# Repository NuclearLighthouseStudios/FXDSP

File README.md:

# FXDSP — A WhateverDSP based guitar pedal

FXDSP is an easily programmable DSP platform in a familiar guitar pedal form factor:

It's based around an STM32F405 microcontroller and runs on the [WhateverDSP framework](https://github.com/NuclearLighthouseStudios/WhateverDSP),
offering low latency audio processing and fully class complicant USB audio and MIDI support.

FXDSP has interchangeable user interface PCBs so it can easily be tailored to the needs of each effect produced on the platform.

For more information about WhateverDSP, [please see the WhateverDSP repository](https://github.com/NuclearLighthouseStudios/WhateverDSP).

## Example code

Here is a full example showing a simple volume control that scales the audio level using a potentiometer:

```c
#include <libwdsp.h>

void wdsp_init(void)
{
	io_digital_out(BYPASS_L, true);
	io_digital_out(BYPASS_R, true);
}

void wdsp_process(float *in_buffer[BLOCK_SIZE], float *out_buffer[BLOCK_SIZE])
{
	float volume = io_analog_in(POT_1);

	for (int i = 0; i < BLOCK_SIZE; i++)
	{
		float l_sample = in_buffer[0][i];
		float r_sample = in_buffer[1][i];

		out_buffer[0][i] = l_sample * volume;
		out_buffer[1][i] = r_sample * volume;
	}
}

```

Check out the [examples repository](https://github.com/NuclearLighthouseStudios/WhateverDSP-Examples) for more,
or [come chat with us on Discord](https://github.com/NuclearLighthouseStudios/FXDSP#chat).

## Chat

[You can chat with us on Discord.](https://discord.gg/WDsFnartXb)

## License

FXDSP hardware is licensed under CC-BY-NC-SA.

The WhateverDSP library is licensed under GNU Lesser General Public License.

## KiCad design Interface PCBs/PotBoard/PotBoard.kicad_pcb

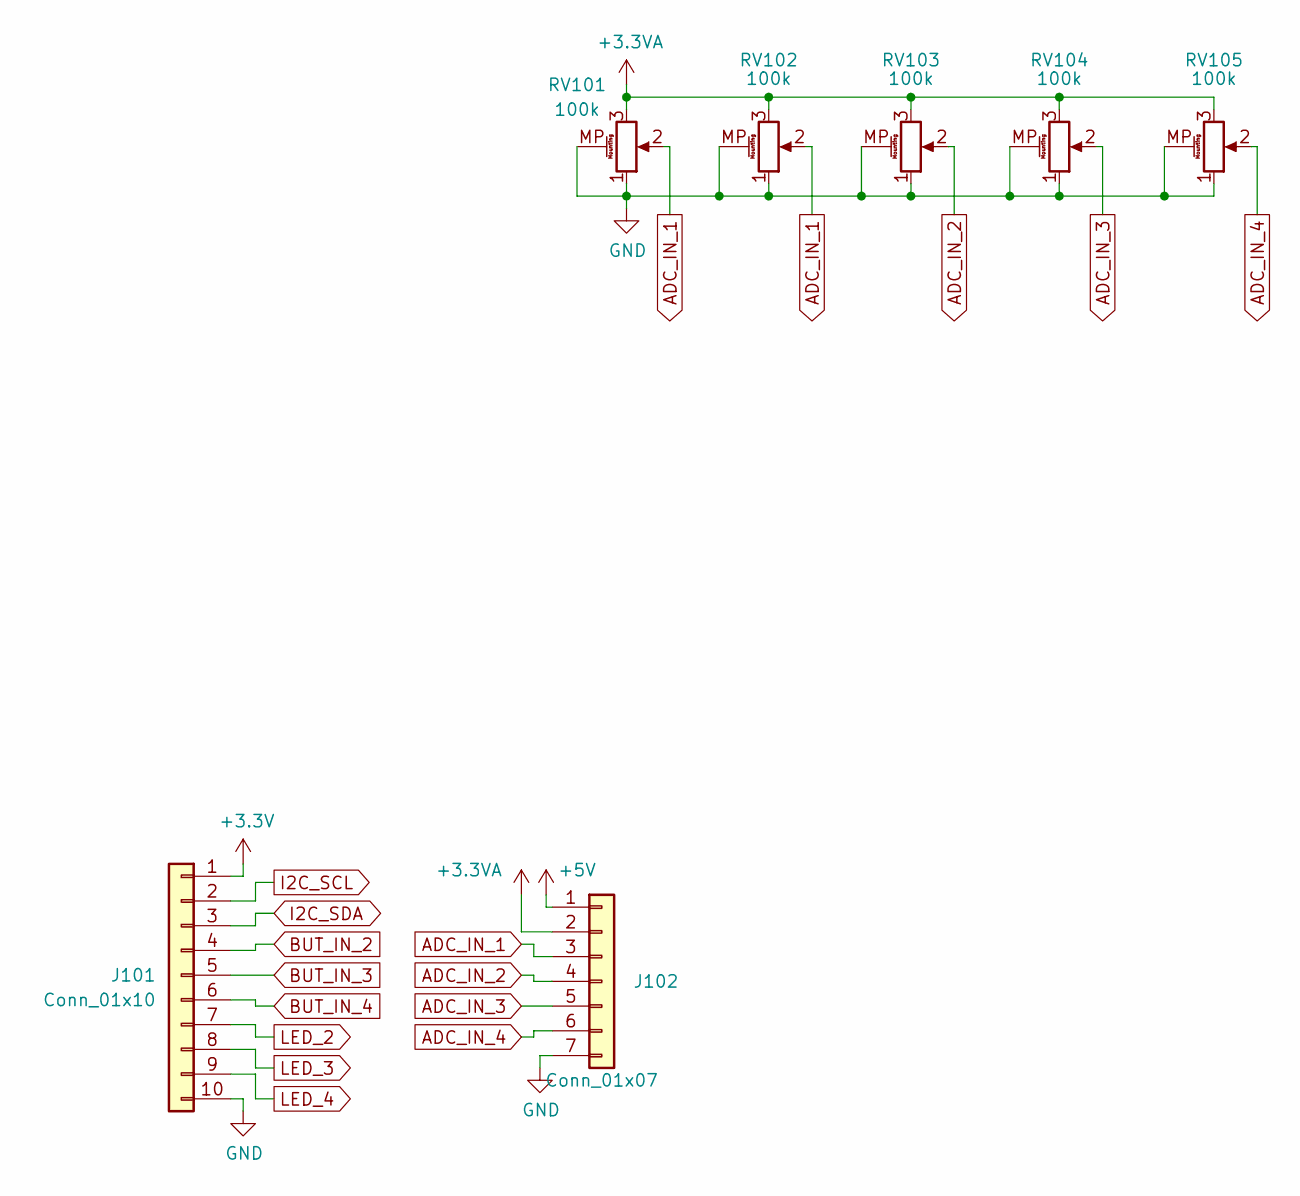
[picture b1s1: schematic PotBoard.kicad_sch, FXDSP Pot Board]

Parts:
J101: Conn_01x10; PinHeader_1x10_P2.54mm_Vertical
J102: Conn_01x07; PinHeader_1x07_P2.54mm_Vertical
RV101, RV102, RV103, RV104, RV105: 100k; Potentiometer_Alps_RK09K_Single_Vertical

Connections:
+3.3V: J101.1
+3.3VA: J102.2, RV101.3, RV102.3, RV103.3, RV104.3, RV105.3
+5V: J102.1
ADC_IN_1: J102.3, RV101.2, RV102.2
ADC_IN_2: J102.4, RV103.2
ADC_IN_3: J102.5, RV104.2
ADC_IN_4: J102.6, RV105.2
BUT_IN_2: J101.4
BUT_IN_3: J101.5
BUT_IN_4: J101.6
GND: J101.10, J102.7, RV101.1, RV101.MP (MountPin), RV102.1, RV102.MP (MountPin), RV103.1, RV103.MP (MountPin), RV104.1, RV104.MP (MountPin), RV105.1, RV105.MP (MountPin)
I2C_SCL: J101.2
I2C_SDA: J101.3
LED_2: J101.7
LED_3: J101.8
LED_4: J101.9

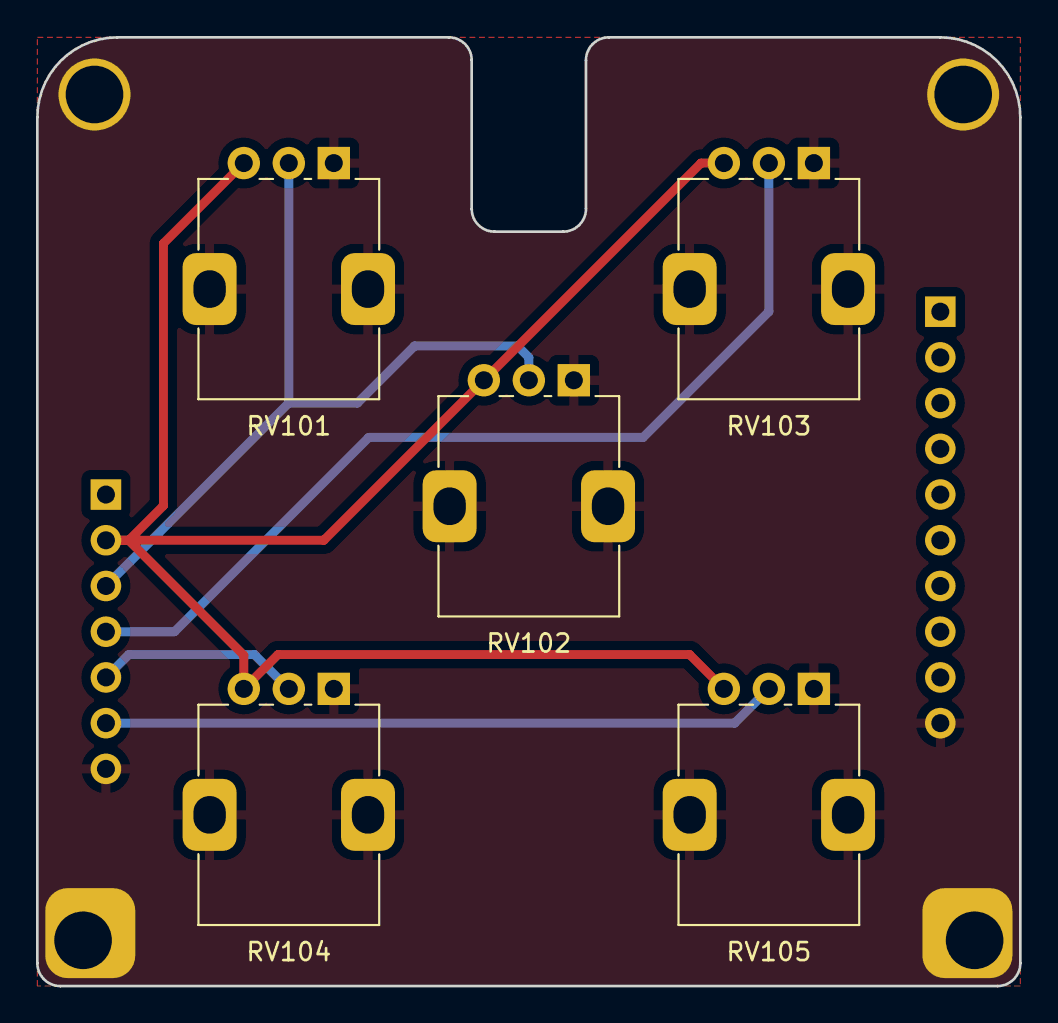
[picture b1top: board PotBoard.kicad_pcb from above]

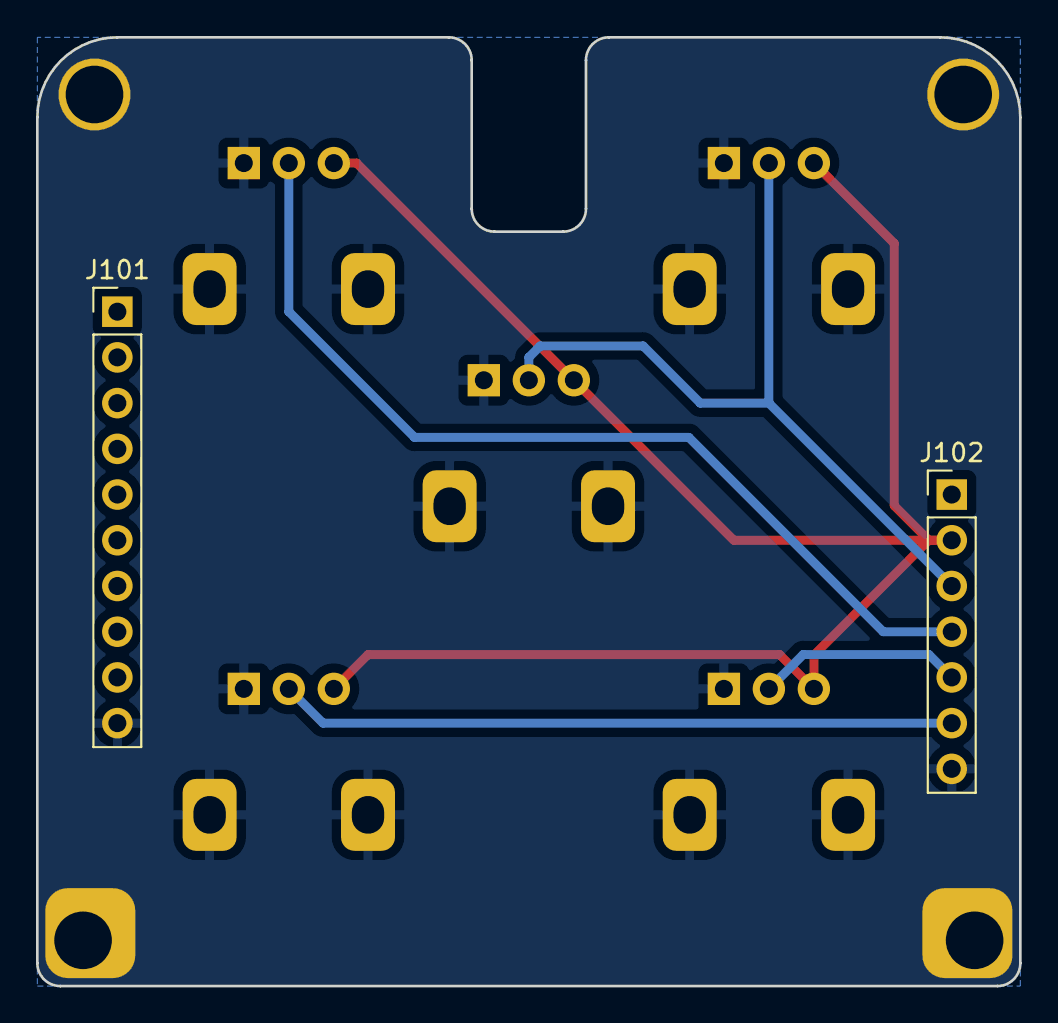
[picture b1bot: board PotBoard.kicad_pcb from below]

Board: 2 copper layers, 54.6 x 52.7 mm, 7 parts (2 on the bottom side), 6 nets.

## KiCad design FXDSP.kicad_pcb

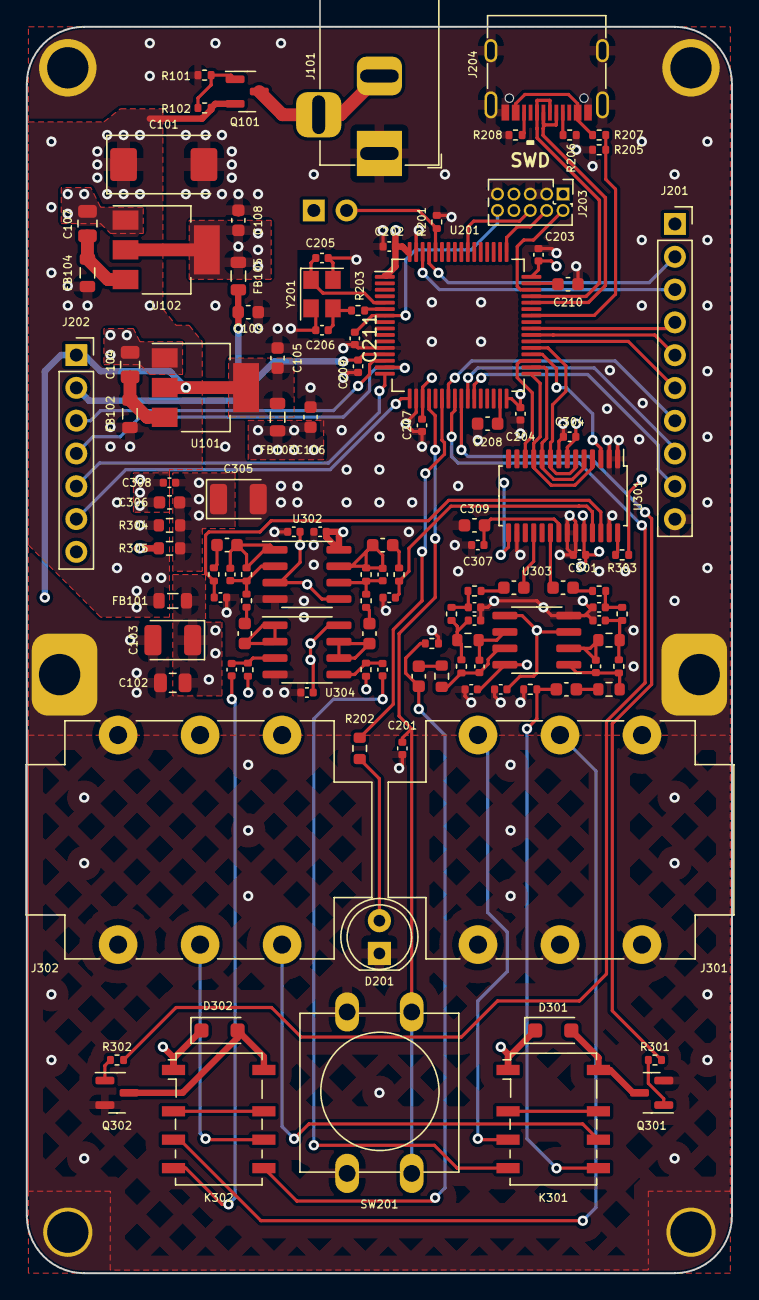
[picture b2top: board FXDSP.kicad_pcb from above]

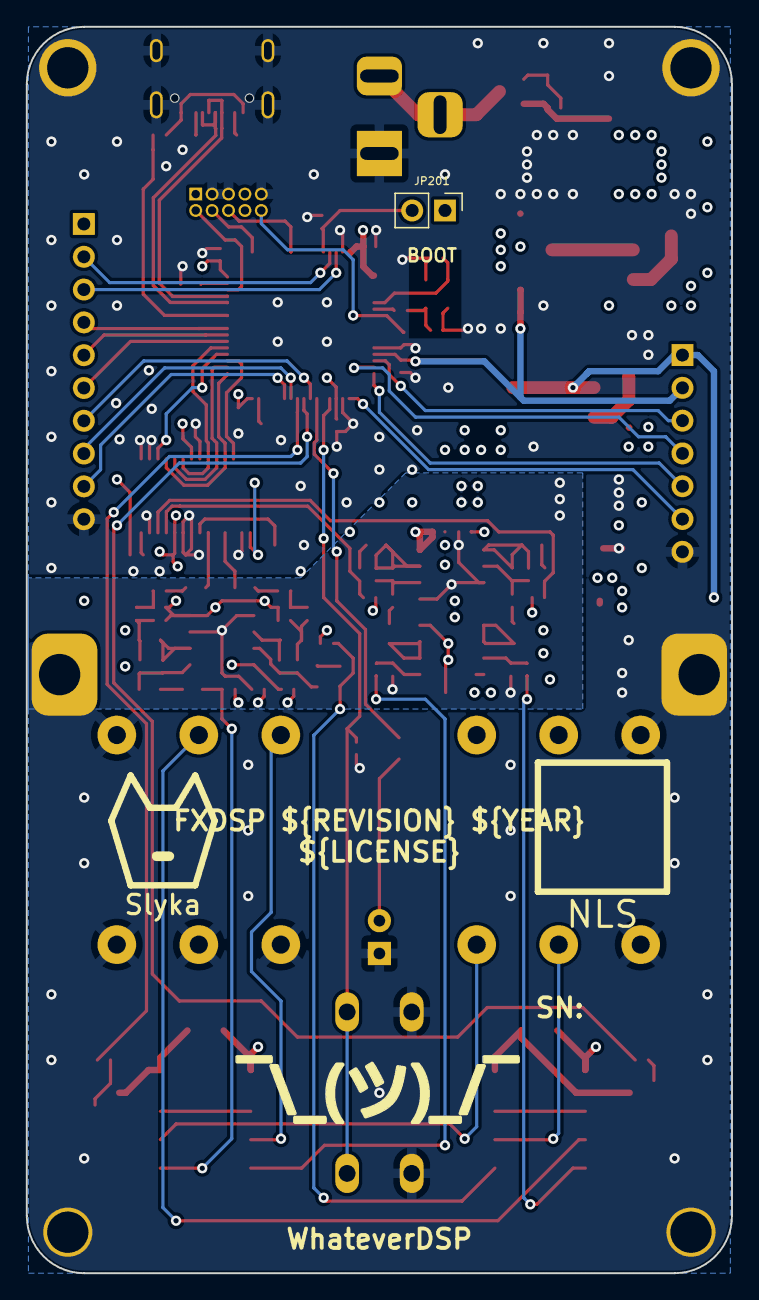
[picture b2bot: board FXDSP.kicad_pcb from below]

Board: 4 copper layers, 54.6 x 96.5 mm, 124 parts (3 on the bottom side), 94 nets.

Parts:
C101: 100µ; CP_EIA-7343-30_AVX-N
C102, C104, C107: 10µ; C_0805_2012Metric
C103: 47µ; CP_EIA-3528-21_Kemet-B
C105, C106, C108, C109, C306, C309, C312, C313, C316, C317, C327, C328, C329, C330: 10µ; C_0603_1608Metric
C201, C202, C203, C204, C207, C209, C211, C301, C302, C303, C304, C307, C308, C322, C325, C326, C331, C332: 100n; C_0402_1005Metric
C205, C206: 12pF; C_0402_1005Metric
C208, C210: 2.2µ; C_0603_1608Metric
C305: 100µ; CP_EIA-3528-21_Kemet-B
C310, C311: 1n; C_0402_1005Metric
C314, C315: 3.3n; C_0402_1005Metric
C318, C319: 150p; C_0402_1005Metric
C320, C321: 330p; C_0402_1005Metric
C323, C324: 10p; C_0402_1005Metric
D201: LED; LED_D5.0mm
D301, D302: SM4007; D_SOD-123F
FB101, FB103, FB105: 600; L_0805_2012Metric
FB102, FB104: 100; L_0805_2012Metric
H101, H102, H103, H104, H105, H106: MountingHole_Pad; MountingHole_3.2mm_M3_Pad
J101: Barrel_Jack_Switch; BarrelJack_Horizontal
J201: Conn_01x10; PinSocket_1x10_P2.54mm_Vertical
J202: Conn_01x07; PinSocket_1x07_P2.54mm_Vertical
J203: Conn_ARM_JTAG_SWD_10; PinHeader_2x05_P1.27mm_Vertical
J204: USB_C_Receptacle_USB2.0; USB_C_Receptacle_G-Switch_GT-USB-7010ASV
J301, J302: AudioJack3_Switch; Jack_6.35mm_Neutrik_NMJ6HCD2_Horizontal
JP201: Boot Jumper; PinHeader_1x02_P2.54mm_Vertical
K301, K302: G6K-2; Relay_DPDT_Omron_G6K-2F-Y
Q101: Si2301CDS; SOT-23
Q301, Q302: MMBT3904; SOT-23
R101: 22k; R_0402_1005Metric
R102, R201, R318, R319: 10k; R_0402_1005Metric
R202: 1k; R_0603_1608Metric
R203: 47; R_0402_1005Metric
R205: 2.2k; R_0402_1005Metric
R206, R208: 5.1k; R_0402_1005Metric
R207, R301, R302, R306, R307: 1k; R_0402_1005Metric
R303: 220k; R_0402_1005Metric
R304, R305: 10k; R_0603_1608Metric
R308, R309: 910; R_0402_1005Metric
R310, R311: 47k; R_0402_1005Metric
R312, R313: 8.6k; R_0402_1005Metric
R314, R316: 43k; R_0402_1005Metric
R315, R317: 130k; R_0603_1608Metric
R320, R321: 100; R_0603_1608Metric
R322, R323, R324, R325: 1M; R_0402_1005Metric
SW201: SW_Push; SW_PUSH-12mm
U101: NCP1117-5.0; SOT-223-3_TabPin2
U102: NCP1117-3.3; SOT-223-3_TabPin2
U201: STM32F405RGTx; LQFP-64_10x10mm_P0.5mm
U301: PCM3060; TSSOP-28_4.4x9.7mm_P0.65mm
U302, U303, U304: NE5532; SOIC-8_3.9x4.9mm_P1.27mm
Y201: 12.288Mhz; Crystal_SMD_3225-4Pin_3.2x2.5mm
foxlogo: foxlogo_nocopper
nlslogo: nlslogo_nocopper

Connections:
+3.3V: C108.1, C202.2, C203.2, C204.2, C207.2, C304.2, FB105.2, J201.1, J203.1 (VTref), JP201.1 (A), R303.1, U102.2 (VO), U201.1 (VBAT), U201.19 (VDD), U201.32 (VDD), U201.48 (VDD), U201.64 (VDD), U301.7 (V_{DD}), U301.15 (~RST)
+3.3VA: C109.1, C209.2, FB105.1, J202.2, U201.13 (VDDA)
+5V: C105.1, D301.1 (K), D302.1 (K), FB103.2, J202.1, K301.1, K302.1, U101.2 (VO)
+5VA: C106.1, C301.2, FB103.1, U301.24 (V_{CC})
+9V: C101.1, FB101.2, FB102.2, FB104.2, Q101.2 (S), R102.2, R304.1
+9VA: C102.1, C103.1, C322.1, C325.1, C326.1, FB101.1, U302.8 (V+), U303.8 (V+), U304.8 (V+)
/Audio/BCK: U201.34 (I2S2_CK), U301.5 (BCK1), U301.10 (BCK2)
/Audio/BYPASSL: R301.1, U201.25 (PC5)
/Audio/BYPASSR: R302.1, U201.24 (PC4)
/Audio/DIN: U201.35 (I2S2_ext_SD), U301.12 (DIN)
/Audio/DOUT: U201.36 (I2S2_SD), U301.3 (DOUT)
/Audio/LRCK: U201.33 (I2S2_WS), U301.4 (LRCK1), U301.11 (LRCK2)
/Audio/SCK: U201.37 (I2S2_MCK), U301.6 (SCKI1), U301.9 (SCKI2)
/V_IN: J101.2, J101.3, Q101.3 (D)
ADC_IN_1: J202.3, U201.14 (ADC1_IN0)
ADC_IN_2: J202.4, U201.15 (ADC1_IN1)
ADC_IN_3: J202.5, U201.16 (ADC1_IN2)
ADC_IN_4: J202.6, U201.17 (ADC1_IN3)
BOOT0: JP201.2 (B), R201.1, U201.60 (BOOT0)
BUT_IN_1: C201.1, SW201.2, U201.20 (PA4)
BUT_IN_2: J201.4, U201.40 (PC9)
BUT_IN_3: J201.5, U201.39 (PC8)
BUT_IN_4: J201.6, U201.38 (PC7)
CODEC_COM: C307.1, C309.1, U301.21 (V_{COM})
COIL_L: D301.2 (A), K301.8, Q301.3 (C)
COIL_R: D302.2 (A), K302.8, Q302.3 (C)
GND: C101.2, C102.2, C103.2, C104.2, C105.2, C106.2, C107.2, C108.2, C109.2, C201.2, C202.1, C203.1, C204.1, C205.2, C206.2, C207.1, C208.2, C209.1, C210.2, C211.2, C301.1, C302.2, C303.2, C304.1, C305.2, C306.2, C307.2, C308.2, C309.2, C310.2, C311.1, C314.2, C315.2, C318.2, C319.2, C322.2, C325.2, C326.2, D201.1 (K), H101.1, H102.1, H103.1, H104.1, H105.1, H106.1, J101.1, J201.10, J202.7, J203.3 (GND), J203.5 (GND), J203.9 (GNDDetect), J204.A1 (GND), J204.A12 (GND), J204.B1 (GND), J204.B12 (GND), J204.S1 (SHIELD), J301.RN, J301.S, J301.SN, J301.TN, J302.S, J302.SN, Q301.2 (E), Q302.2 (E), R101.2, R201.2, R205.2, R206.2, R208.2, R305.2, R324.2, R325.2, SW201.1, U101.1 (GND), U102.1 (GND), U201.12 (VSSA), U201.18 (VSS), U201.63 (VSS), U301.1 (MC/SCL/FMT), U301.2 (MD/SDA/DEMP), U301.8 (DGND), U301.16 (SGND), U301.22 (AGND2), U301.23 (AGND1), U301.27 (~MS/ADR/IFMD), U302.4 (V-), U303.4 (V-), U304.4 (V-), Y201.2, Y201.4
GNDA: C302.1, C303.1, C305.1, C306.1, C308.1, R304.2, R305.1, R322.1, R323.1, U302.3 (+), U302.5 (+), U303.3 (+), U303.5 (+)
I2C_SCL: J201.2, U201.61 (I2C1_SCL)
I2C_SDA: J201.3, U201.62 (I2C1_SDA)
LED_1: R202.2, U201.22 (TIM3_CH1)
LED_2: J201.7, U201.23 (TIM3_CH2)
LED_3: J201.8, U201.26 (TIM3_CH3)
LED_4: J201.9, U201.27 (TIM3_CH4)
NRST: C211.1, J203.10 (~RESET), U201.7 (NRST)
unnamed: C104.1, FB102.1, U101.3 (VI)
unnamed: C107.1, FB104.1, U102.3 (VI)
unnamed: C206.1, R203.2, Y201.3
unnamed: C312.2, R308.2
unnamed: C313.2, R309.2
unnamed: C314.1, R308.1, R310.2
unnamed: C315.1, R309.1, R311.2
unnamed: C316.1, C320.2, R312.2, U302.7
unnamed: C316.2, R306.1
unnamed: C317.1, C321.2, R313.2, U302.1
unnamed: C317.2, R307.1
unnamed: C318.1, R310.1, R314.2, R315.2
unnamed: C319.1, R311.1, R316.2, R317.2
unnamed: C323.1, R314.1, R320.2, U303.1
unnamed: C324.1, R316.1, R321.2, U303.7
unnamed: C327.2, R318.1
unnamed: C328.2, R319.1
unnamed: C329.1, R320.1
unnamed: C329.2, K301.5, R324.1
unnamed: C330.1, R321.1
unnamed: C330.2, K302.5, R325.1
unnamed: C331.2, K301.4
unnamed: C332.2, K302.4
unnamed: D201.2 (A), R202.1
unnamed: J204.A5 (CC1), R206.1
unnamed: J204.B5 (CC2), R208.1
unnamed: J204.A4 (VBUS), J204.A9 (VBUS), J204.B4 (VBUS), J204.B9 (VBUS), R207.1
unnamed: J301.R, K302.3
unnamed: J301.T, K301.3
unnamed: J302.R, K302.6
unnamed: J302.T, K301.6
unnamed: K301.2, K301.7
unnamed: K302.2, K302.7
unnamed: Q101.1 (G), R101.1, R102.1
unnamed: Q301.1 (B), R301.2
unnamed: Q302.1 (B), R302.2
unnamed: C205.1, U201.5 (RCC_OSC_IN), Y201.1
unnamed: R203.1, U201.6 (RCC_OSC_OUT)
unnamed: C208.1, U201.31 (VCAP_1)
unnamed: C210.1, U201.47 (VCAP_2)
unnamed: R303.2, U301.28 (MODE)
unnamed: C310.1, R306.2, U301.25 (V_{IN}L)
unnamed: C311.2, R307.2, U301.26 (V_{IN}R)
unnamed: C312.1, U301.20 (V_{OUT}L+)
unnamed: C313.1, U301.18 (V_{OUT}R+)
unnamed: C321.1, R313.1, R319.2, U302.2 (-)
unnamed: C320.1, R312.1, R318.2, U302.6 (-)
unnamed: C323.2, R315.1, U303.2 (-)
unnamed: C324.2, R317.1, U303.6 (-)
unnamed: C332.1, R323.2, U304.3 (+)
unnamed: C328.1, U304.1, U304.2 (-)
unnamed: C331.1, R322.2, U304.5 (+)
unnamed: C327.1, U304.6 (-), U304.7
SWCLK: J203.4 (SWDCLK/TCK), U201.49 (SYS_JTCK-SWCLK)
SWDIO: J203.2 (SWDIO/TMS), U201.46 (SYS_JTMS-SWDIO)
SWO: J203.6 (SWO/TDO), U201.55 (SYS_JTDO-SWO)
USB_D+: J204.A6 (D+), J204.B6 (D+), U201.45 (USB_OTG_FS_DP)
USB_D-: J204.A7 (D-), J204.B7 (D-), U201.44 (USB_OTG_FS_DM)
USB_VBUS: R205.1, R207.2, U201.42 (USB_OTG_FS_VBUS)

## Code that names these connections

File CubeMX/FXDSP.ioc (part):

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Mcu.Name=STM32F405RGTx
Mcu.Package=LQFP64
Mcu.UserName=STM32F405RGTx
PA0-WKUP.Signal=ADCx_IN0
PA1.Signal=ADCx_IN1
PA11.Mode=Device_Only
PA11.Signal=USB_OTG_FS_DM
PA12.Mode=Device_Only
PA12.Signal=USB_OTG_FS_DP
PA13.Mode=Trace_Asynchronous_SW
PA13.Signal=SYS_JTMS-SWDIO
PA14.Mode=Trace_Asynchronous_SW
PA14.Signal=SYS_JTCK-SWCLK
PA2.Signal=ADCx_IN2
PA3.Signal=ADCx_IN3
PA4.GPIOParameters=GPIO_Label
PA4.GPIO_Label=BUTTON_1
PA4.Signal=GPIO_Input
PA6.GPIOParameters=GPIO_Label
PA6.GPIO_Label=LED_1
PA6.Signal=S_TIM3_CH1
PA7.GPIOParameters=GPIO_Label
PA7.GPIO_Label=LED_2
PA7.Signal=S_TIM3_CH2
PA9.Mode=Activate_VBUS
PA9.Signal=USB_OTG_FS_VBUS
PB0.GPIOParameters=GPIO_Label
PB0.GPIO_Label=LED_3
PB0.Signal=S_TIM3_CH3
PB1.GPIOParameters=GPIO_Label
PB1.GPIO_Label=LED_4
PB1.Signal=S_TIM3_CH4
PB12.Mode=Full_Duplex_Master
PB12.Signal=I2S2_WS
PB13.Mode=Full_Duplex_Master
PB13.Signal=I2S2_CK
PB14.Mode=Full_Duplex_Master
PB14.Signal=I2S2_ext_SD
PB15.Mode=Full_Duplex_Master
PB15.Signal=I2S2_SD
PB3.Mode=Trace_Asynchronous_SW
PB3.Signal=SYS_JTDO-SWO
PB8.Mode=I2C
PB8.Signal=I2C1_SCL
PB9.Mode=I2C
PB9.Signal=I2C1_SDA
PC4.GPIOParameters=GPIO_Label
PC4.GPIO_Label=BYPASS_R
PC4.Signal=GPIO_Output
PC5.GPIOParameters=GPIO_Label
PC5.GPIO_Label=BYPASS_L
PC5.Signal=GPIO_Output
PC6.Mode=Master_Clock_Activated
PC6.Signal=I2S2_MCK
PC7.GPIOParameters=GPIO_Label
PC7.GPIO_Label=BUTTON_4
PC7.Signal=GPIO_Input
PC8.GPIOParameters=GPIO_Label
PC8.GPIO_Label=BUTTON_3
PC8.Signal=GPIO_Input
PC9.GPIOParameters=GPIO_Label
PC9.GPIO_Label=BUTTON_2
PC9.Signal=GPIO_Input
PH0-OSC_IN.Mode=HSE-External-Oscillator
PH0-OSC_IN.Signal=RCC_OSC_IN
PH1-OSC_OUT.Mode=HSE-External-Oscillator
PH1-OSC_OUT.Signal=RCC_OSC_OUT
RCC.HSE_VALUE=12288000
RCC.SYSCLKFreq_VALUE=167936000
RCC.SYSCLKSource=RCC_SYSCLKSOURCE_PLLCLK
board=custom

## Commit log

2023-04-02 Initial Commit of FXDSP board
    Added WDSP logo and serial number field missing from version ordered
    from JLCPCB
2023-04-02 Update gitignore
2023-05-14 Fix reset problems from r01 PCB
2023-05-14 Add PotBoard interface PCB
2023-05-14 Add basic readme
2023-05-15 Create LICENSE
2023-05-15 Remove LICENSE
2023-05-20 Correct positioning of lower potentiometers on interface PCB
2023-05-29 Update README and add LICENSE

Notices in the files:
parts and their libraries:
LICENSE: CC BY-NC-SA
